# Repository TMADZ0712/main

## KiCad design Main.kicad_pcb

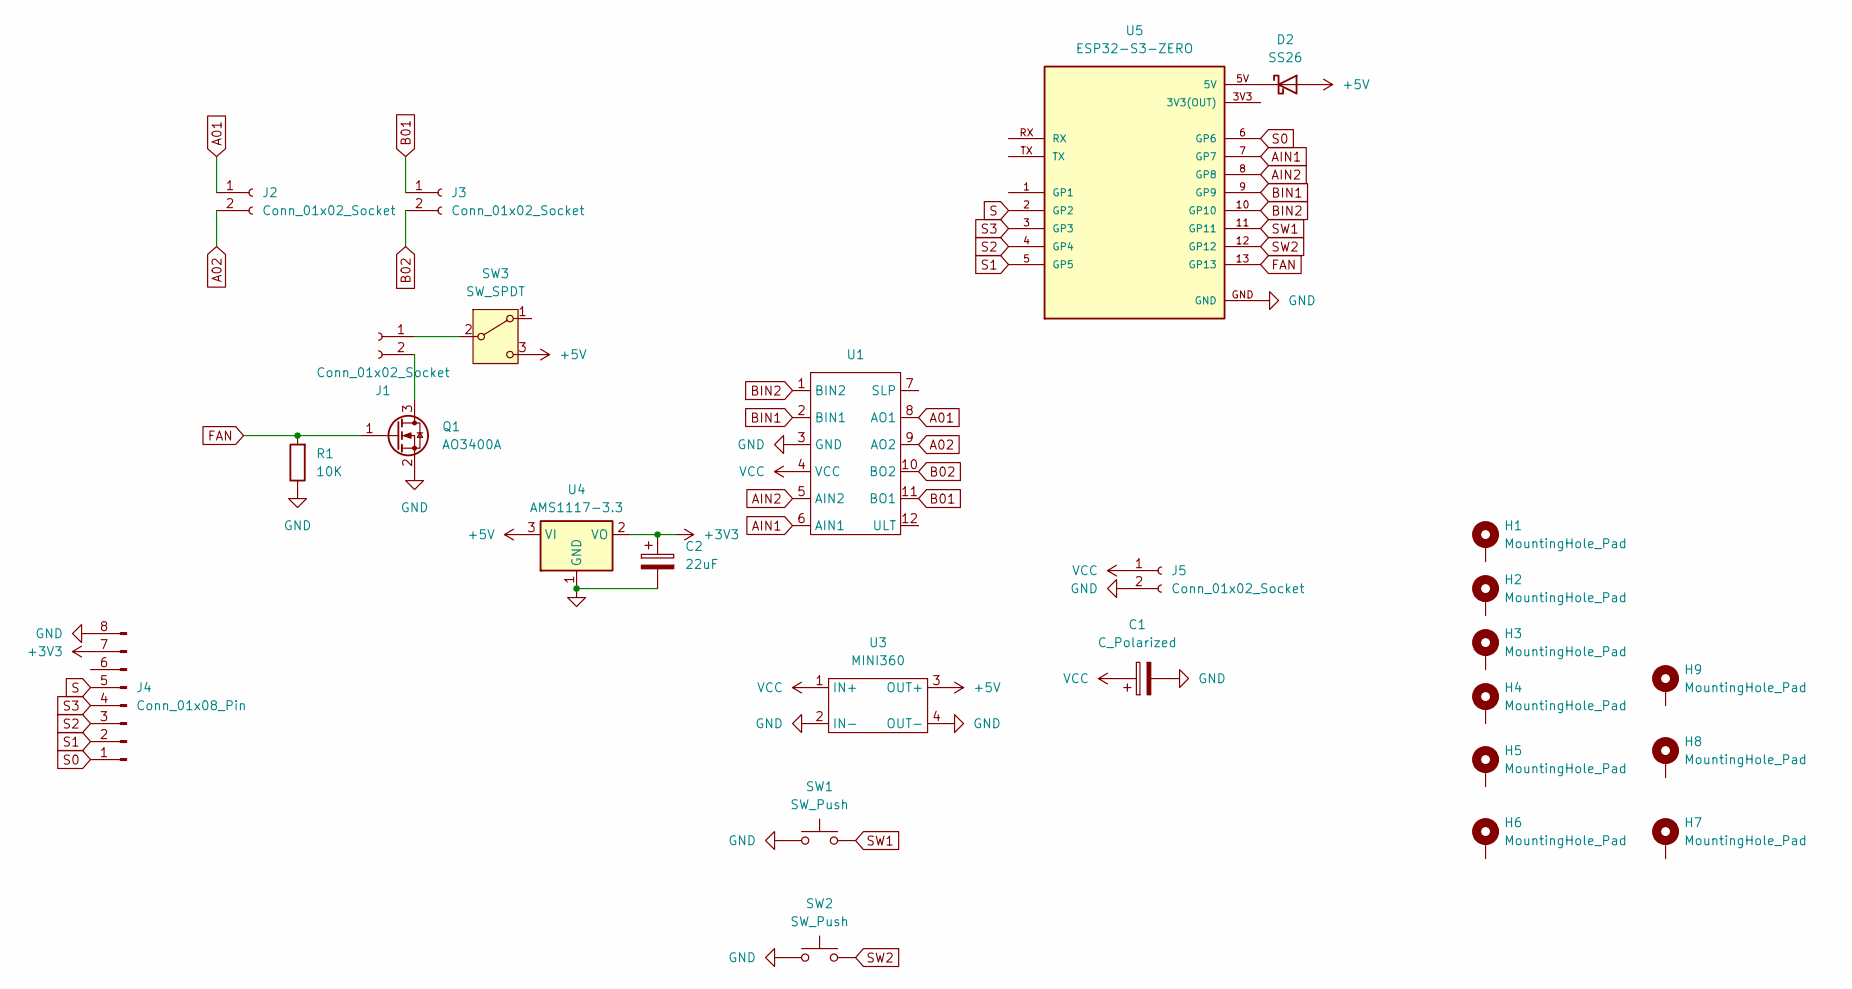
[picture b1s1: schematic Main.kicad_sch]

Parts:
C1: C_Polarized; CP_Elec_6.3x5.8
C2: 22uF; CP_EIA-3216-12_Kemet-S_HandSolder
D2: SS26; D_SMA
H1, H2, H3, H4, H5, H6, H7, H8, H9: MountingHole_Pad; MountingHole_2.5mm
J1, J2, J3: Conn_01x02_Socket; PinHeader_1x02_P2.54mm_Vertical
J4: Conn_01x08_Pin; PinSocket_1x08_P2.54mm_Vertical
J5: Conn_01x02_Socket; PinSocket_1x02_P2.54mm_Vertical
Q1: AO3400A; SOT-23
R1: 10K; R_0805_2012Metric_Pad1.20x1.40mm_HandSolder
SW1, SW2: SW_Push; SW_PUSH_6mm
SW3: SW_SPDT; SW_Slide_SPDT_Straight_CK_OS102011MS2Q
U1: Untitled
U3: MINI360; Mini360
U4: AMS1117-3.3; SOT-223-3_TabPin2
U5: ESP32-S3-ZERO; MODULE_ESP32-S3-ZERO; MPN ESP32-S3-Zero

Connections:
+3V3: C2.1, J4.7, U4.2 (VO)
+5V: D2.2 (A), SW3.3 (C), U3.3 (OUT+), U4.3 (VI)
A01: J2.1, U1.8 (AO1)
A02: J2.2, U1.9 (AO2)
AIN1: U1.6 (AIN1), U5.7 (GP7)
AIN2: U1.5 (AIN2), U5.8 (GP8)
B01: J3.1, U1.11 (BO1)
B02: J3.2, U1.10 (BO2)
BIN1: U1.2 (BIN1), U5.9 (GP9)
BIN2: U1.1 (BIN2), U5.10 (GP10)
FAN: Q1.1 (G), R1.2, U5.13 (GP13)
GND: C1.2, C2.2, J4.8, J5.2, Q1.2 (S), R1.1, SW1.1, SW2.1, U1.3 (GND), U3.2 (IN-), U3.4 (OUT-), U4.1 (GND), U5.GND
unnamed: D2.1 (K), U5.5V
unnamed: J1.1, SW3.2 (B)
unnamed: J1.2, Q1.3 (D)
S: J4.5, U5.2 (GP2)
S0: J4.1, U5.6 (GP6)
S1: J4.2, U5.5 (GP5)
S2: J4.3, U5.4 (GP4)
S3: J4.4, U5.3 (GP3)
SW1: SW1.2, U5.11 (GP11)
SW2: SW2.2, U5.12 (GP12)
VCC: C1.1, J5.1, U1.4 (VCC), U3.1 (IN+)

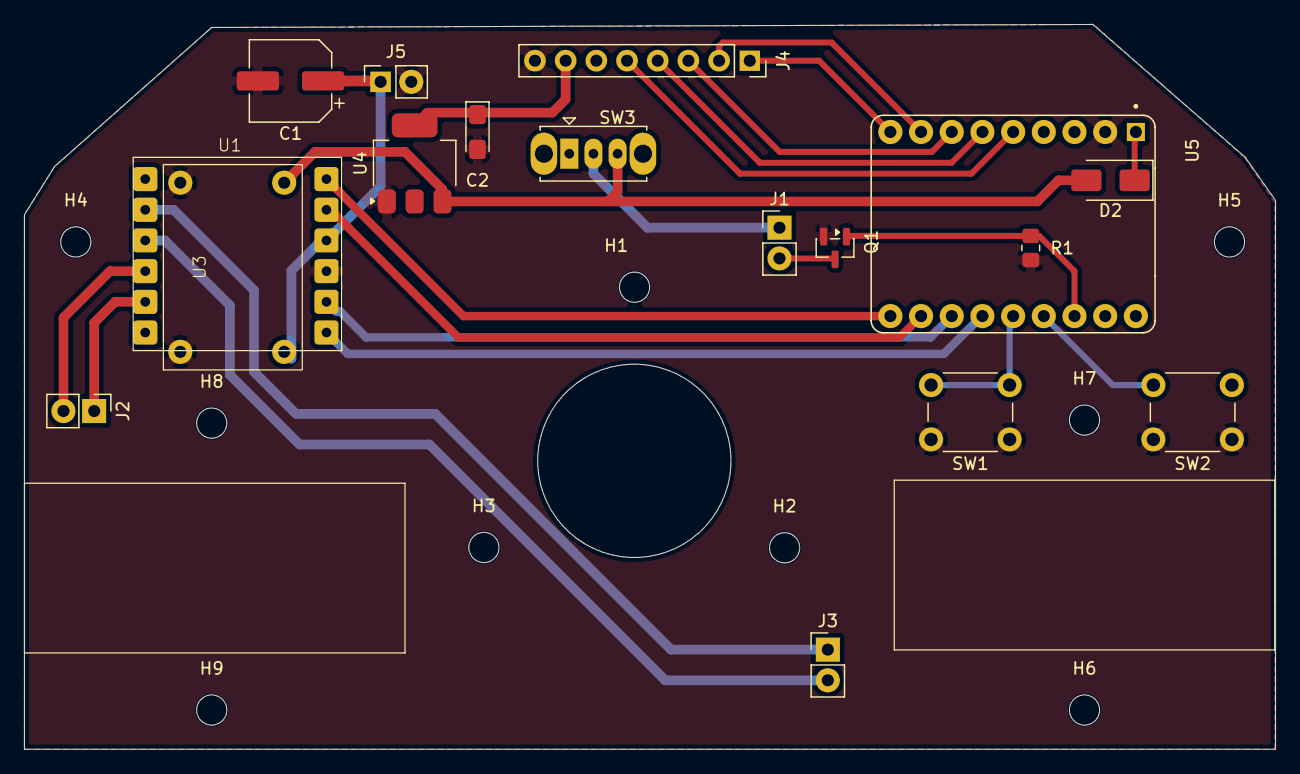
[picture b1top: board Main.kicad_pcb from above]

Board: 2 copper layers, 103.6 x 60.0 mm, 26 parts (0 on the bottom side), 23 nets.
